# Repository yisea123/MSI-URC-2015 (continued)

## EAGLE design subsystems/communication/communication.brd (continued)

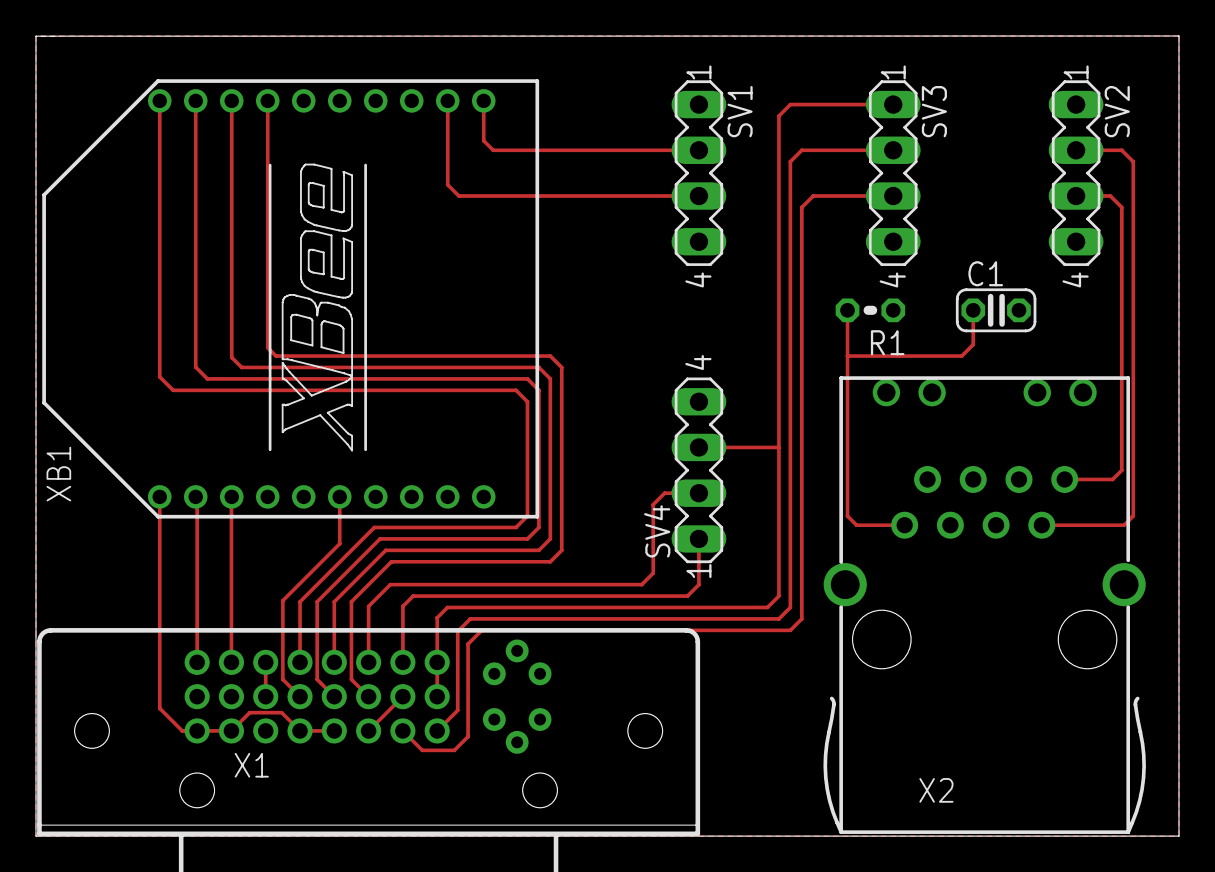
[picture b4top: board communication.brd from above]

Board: 2 copper layers, 63.5 x 44.5 mm, 9 parts (0 on the bottom side), 19 nets.

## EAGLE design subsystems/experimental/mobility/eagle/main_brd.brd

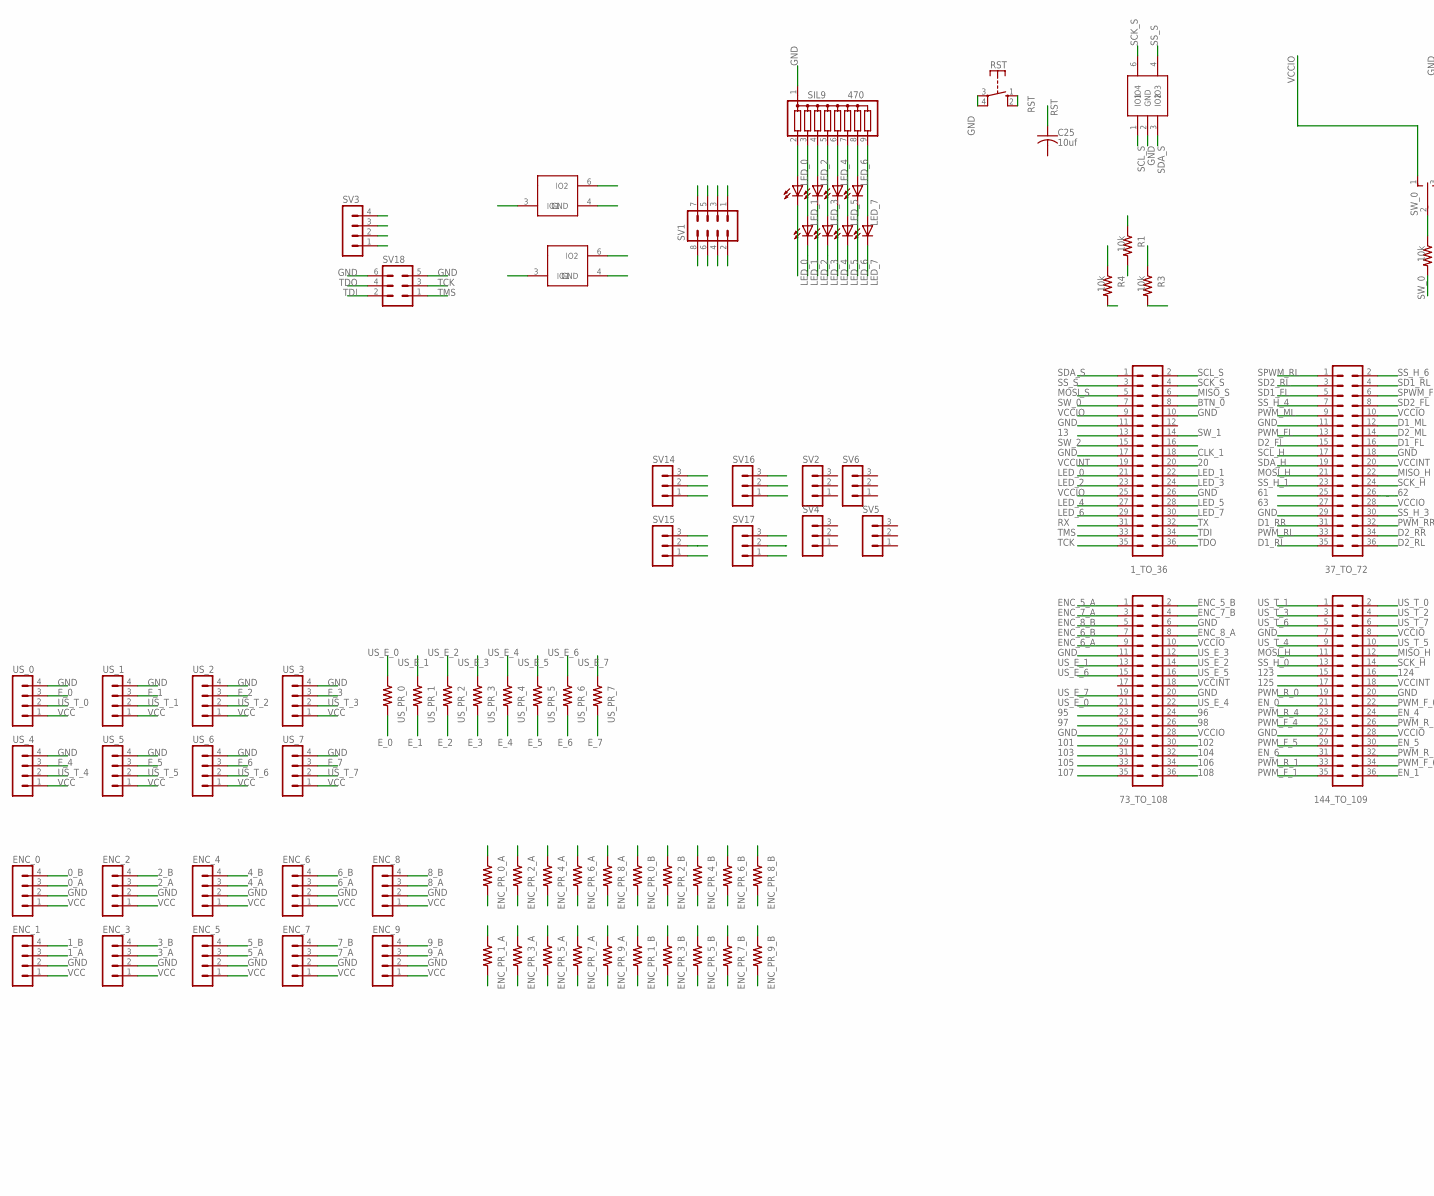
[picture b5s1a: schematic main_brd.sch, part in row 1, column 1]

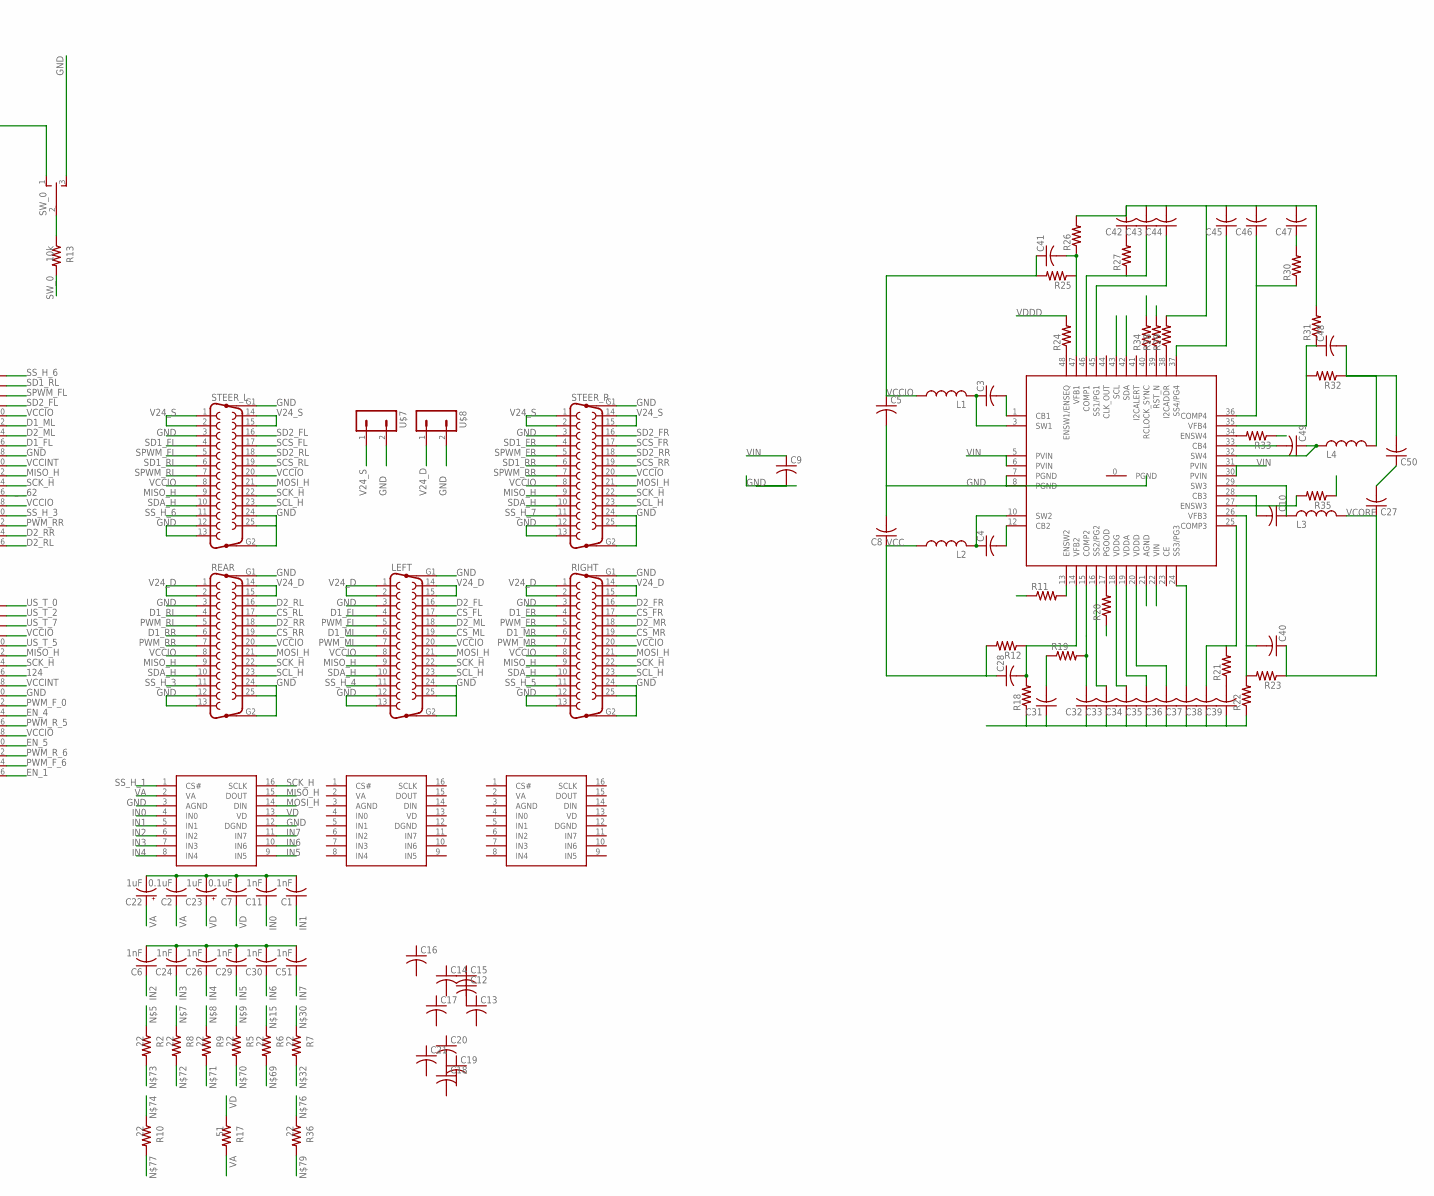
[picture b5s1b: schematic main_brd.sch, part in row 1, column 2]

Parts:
1_TO_36, 37_TO_72, 73_TO_108, 144_TO_109: MA18-2
C1, C6, C11, C24, C26, C29, C30, C51: 1nF; C1206
C2, C7: 0.1uF; C1206
C3, C4, C5, C8, C9, C10, C12, C13, C14, C15, C16, C17, C18, C19, C20, C21, C27, C28, C31, C32, C33, C34, C35, C36, C37, C38, C39, C40, C41, C42, C43, C44, C45, C46, C47, C48, C49, C50: C-USC1206; C1206
C22, C23: 1uF; E1,8-4
C25: 10uf; C1206
ENC_0, ENC_1, ENC_2, ENC_3, ENC_4, ENC_5, ENC_6, ENC_7, ENC_8, ENC_9: MA04-1
ENC_PR_0_A, ENC_PR_0_B, ENC_PR_1_A, ENC_PR_1_B, ENC_PR_2_A, ENC_PR_2_B, ENC_PR_3_A, ENC_PR_3_B, ENC_PR_4_A, ENC_PR_4_B, ENC_PR_5_A, ENC_PR_5_B, ENC_PR_6_A, ENC_PR_6_B, ENC_PR_7_A, ENC_PR_7_B, ENC_PR_8_A, ENC_PR_8_B, ENC_PR_9_A, ENC_PR_9_B: R-US_R1206; R1206
L1, L2, L3, L4: L-USL1206; C1206
LED_0, LED_1, LED_2, LED_3, LED_4, LED_5, LED_6, LED_7: LEDSMT1206; 1206
LEFT: F25HP
R1, R3, R4, R13: 10k; R1206
R2, R5, R6, R7, R8, R9, R10, R36: 22; R1206
R11, R12, R18, R19, R20, R21, R22, R23, R24, R25, R26, R27, R28, R29, R30, R31, R32, R33, R34, R35: R-US_R1206; R1206
R17: 51; R1206
REAR: F25HP
RIGHT: F25HP
RST: RACON12
SIL9: 470; SIL9
STEER_L: F25HP
STEER_R: F25HP
SV1: MA04-2
SV2, SV4, SV5, SV6, SV14, SV15, SV16, SV17: MA03-1
SV3: MA04-1
SV18: MA03-2
SW_0: TL39PO; TL3XPO
U$1: TPD4E1B06DCKR; DCK6
U$2: TPS65400RGZR; VQFN48
U$4, U$5: TPD2E2U06DRLR; DRL5
U$7, U$8: MB02-1; MB03-1
U$9, U$10, U$11: ADC128S052QCMT; R-PDSO-G16
US_0, US_1, US_2, US_3, US_4, US_5, US_6, US_7: MA04-1
US_PR_0, US_PR_1, US_PR_2, US_PR_3, US_PR_4, US_PR_5, US_PR_6, US_PR_7: R-US_R1206; R1206

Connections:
0_A: ENC_0.3, ENC_PR_0_A.2
0_B: ENC_0.4, ENC_PR_0_B.2
1_A: ENC_1.3, ENC_PR_1_A.2
1_B: ENC_1.4, ENC_PR_1_B.2
2_A: ENC_2.3, ENC_PR_2_A.2
2_B: ENC_2.4, ENC_PR_2_B.2
3_A: ENC_3.3, ENC_PR_3_A.2
3_B: ENC_3.4, ENC_PR_3_B.2
4_A: ENC_4.3, ENC_PR_4_A.2
4_B: ENC_4.4, ENC_PR_4_B.2
5_A: ENC_5.3, ENC_PR_5_A.2
5_B: ENC_5.4, ENC_PR_5_B.2
6_A: ENC_6.3, ENC_PR_6_A.2
6_B: ENC_6.4, ENC_PR_6_B.2
7_A: ENC_7.3, ENC_PR_7_A.2
7_B: ENC_7.4, ENC_PR_7_B.2
8_A: ENC_8.3, ENC_PR_8_A.2
8_B: ENC_8.4, ENC_PR_8_B.2
9_A: ENC_9.3, ENC_PR_9_A.2
9_B: ENC_9.4, ENC_PR_9_B.2
13: 1_TO_36.13
20: 1_TO_36.20
61: 37_TO_72.25
62: 37_TO_72.26
63: 37_TO_72.27
95: 73_TO_108.23
96: 73_TO_108.24
97: 73_TO_108.25
98: 73_TO_108.26
101: 73_TO_108.29
102: 73_TO_108.30
103: 73_TO_108.31
104: 73_TO_108.32
105: 73_TO_108.33
106: 73_TO_108.34
107: 73_TO_108.35
108: 73_TO_108.36
123: 144_TO_109.15
124: 144_TO_109.16
125: 144_TO_109.17
BTN: U$4.6 (IO2)
BTN_0: 1_TO_36.8
CLK_1: 1_TO_36.18
CS_FL: LEFT.17
CS_FR: RIGHT.17
CS_ML: LEFT.19
CS_MR: RIGHT.19
CS_RL: REAR.17
CS_RR: REAR.19
D1_FL: 37_TO_72.16, LEFT.4
D1_FR: RIGHT.4
D1_ML: 37_TO_72.12, LEFT.6
D1_MR: RIGHT.6
D1_RL: 37_TO_72.35, REAR.4
D1_RR: 37_TO_72.31, REAR.6
D2_FL: 37_TO_72.15, LEFT.16
D2_FR: RIGHT.16
D2_ML: 37_TO_72.14, LEFT.18
D2_MR: RIGHT.18
D2_RL: 37_TO_72.36, REAR.16
D2_RR: 37_TO_72.34, REAR.18
ENC_0_A: ENC_PR_0_A.1
ENC_0_B: ENC_PR_0_B.1
ENC_1_A: ENC_PR_1_A.1
ENC_1_B: ENC_PR_1_B.1
ENC_2_A: ENC_PR_2_A.1
ENC_2_B: ENC_PR_2_B.1
ENC_3_A: ENC_PR_3_A.1
ENC_3_B: ENC_PR_3_B.1
ENC_4_A: ENC_PR_4_A.1
ENC_4_B: ENC_PR_4_B.1
ENC_5_A: 73_TO_108.1, ENC_PR_5_A.1
ENC_5_B: 73_TO_108.2, ENC_PR_5_B.1
ENC_6_A: 73_TO_108.9, ENC_PR_6_A.1
ENC_6_B: 73_TO_108.7, ENC_PR_6_B.1
ENC_7_A: 73_TO_108.3, ENC_PR_7_A.1
ENC_7_B: 73_TO_108.4, ENC_PR_7_B.1
ENC_8_A: 73_TO_108.8, ENC_PR_8_A.1
ENC_8_B: 73_TO_108.5, ENC_PR_8_B.1
ENC_9_A: ENC_PR_9_A.1
ENC_9_B: ENC_PR_9_B.1
ENSW3: R35.2, U$2.27 (ENSW3)
ENSW4: R33.2, U$2.34 (ENSW4)
EN_0: 144_TO_109.21
EN_1: 144_TO_109.36
EN_4: 144_TO_109.24
EN_5: 144_TO_109.30
EN_6: 144_TO_109.31
E_0: US_0.3, US_PR_0.2
E_1: US_1.3, US_PR_1.2
E_2: US_2.3, US_PR_2.2
E_3: US_3.3, US_PR_3.2
E_4: US_4.3, US_PR_4.2
E_5: US_5.3, US_PR_5.2
E_6: US_6.3, US_PR_6.2
E_7: US_7.3, US_PR_7.2
GND: 1_TO_36.10, 1_TO_36.11, 1_TO_36.17, 1_TO_36.26, 37_TO_72.11, 37_TO_72.18, 37_TO_72.29, 73_TO_108.6, 73_TO_108.11, 73_TO_108.20, 73_TO_108.27, 144_TO_109.7, 144_TO_109.20, 144_TO_109.27, C1.2, C2.2, C5.2, C7.2, C8.2, C9.2, C11.2, C22.-, C23.-, C27.2, C31.1, C32.1, C33.1, C34.1, C35.1, C36.1, C37.1, C38.1, C39.1, C42.2, C43.2, C44.2, C45.2, C46.2, C47.2, ENC_0.2, ENC_1.2, ENC_2.2, ENC_3.2, ENC_4.2, ENC_5.2, ENC_6.2, ENC_7.2, ENC_8.2, ENC_9.2, LEFT.3, LEFT.12, LEFT.13, LEFT.24, LEFT.25, LEFT.G1, LEFT.G2, R18.1, R22.1, R26.2, R29.2, R31.2, R34.2, REAR.3, REAR.12, REAR.13, REAR.24, REAR.25, REAR.G1, REAR.G2, RIGHT.3, RIGHT.12, RIGHT.13, RIGHT.24, RIGHT.25, RIGHT.G1, RIGHT.G2, RST.3, RST.4, SIL9.1, STEER_L.3, STEER_L.12, STEER_L.13, STEER_L.24, STEER_L.25, STEER_L.G1, STEER_L.G2, STEER_R.3, STEER_R.12, STEER_R.13, STEER_R.24, STEER_R.25, STEER_R.G1, STEER_R.G2, SV1.7, SV1.8, SV3.2, SV14.3, SV15.3, SV16.3, SV17.3, SV18.5, SV18.6, SW_0.3 (S), U$1.2 (GND), U$2.7 (PGND), U$2.8 (PGND), U$2.21 (AGND), U$4.4 (GND), U$5.4 (GND), U$7.2, U$8.2, U$9.3 (AGND), U$9.12 (DGND), US_0.4, US_1.4, US_2.4, US_3.4, US_4.4, US_5.4, US_6.4, US_7.4
IN0: C11.1, U$9.4 (IN0)
IN1: C1.1, U$9.5 (IN1)
IN2: C6.1, U$9.6 (IN2)
IN3: C24.1, U$9.7 (IN3)
IN4: C26.1, U$9.8 (IN4)
IN5: C29.1, U$9.9 (IN5)
IN6: C30.1, U$9.10 (IN6)
IN7: C51.1, U$9.11 (IN7)
LED_0: 1_TO_36.21, LED_0.C
LED_1: 1_TO_36.22, LED_1.C
LED_2: 1_TO_36.23, LED_2.C
LED_3: 1_TO_36.24, LED_3.C
LED_4: 1_TO_36.27, LED_4.C
LED_5: 1_TO_36.28, LED_5.C
LED_6: 1_TO_36.29, LED_6.C
LED_7: 1_TO_36.30, LED_7.C
MISO_H: 37_TO_72.22, 144_TO_109.12, LEFT.9, REAR.9, RIGHT.9, STEER_L.9, STEER_R.9, U$9.15 (DOUT)
MISO_S: 1_TO_36.6, SV1.5, U$5.3 (IO1)
MOSI_H: 37_TO_72.21, 144_TO_109.11, LEFT.21, REAR.21, RIGHT.21, STEER_L.21, STEER_R.21, U$9.14 (DIN)
MOSI_S: 1_TO_36.5, SV1.6, U$5.6 (IO2)
unnamed: C4.1, L2.2, U$2.10 (SW2)
unnamed: C18.1, C20.2
unnamed: C3.2, U$2.1 (CB1)
unnamed: C3.1, L1.2, U$2.3 (SW1)
unnamed: C4.2, U$2.12 (CB2)
unnamed: C10.1, L3.2, U$2.29 (SW3)
unnamed: C10.2, U$2.28 (CB3)
unnamed: R11.2, U$2.13 (ENSW2)
unnamed: C28.2, R12.1, R18.2, U$2.14 (VFB2)
unnamed: C32.2, R19.2, U$2.15 (COMP2)
unnamed: LED_0.A, SIL9.2
unnamed: LED_4.A, SIL9.6
unnamed: LED_6.A, SIL9.8
unnamed: LED_1.A, SIL9.3
unnamed: LED_3.A, SIL9.5
unnamed: LED_5.A, SIL9.7
unnamed: LED_7.A, SIL9.9
unnamed: C31.2, R19.1
unnamed: R13.1, SW_0.2
unnamed: R20.2, U$2.17 (PGOOD)
unnamed: C6.2, C24.2, C26.2, C29.2, C30.2, C51.2
unnamed: C34.2, U$2.18 (VDDG)
unnamed: C35.2, U$2.19 (VDDA)
unnamed: C39.2, R21.1
unnamed: C40.2, R22.2, R23.2, U$2.26 (VFB3)
unnamed: C38.2, R21.2, U$2.25 (COMP3)
unnamed: R24.1, U$2.48 (ENSW1/ENSEQ)
unnamed: C37.2, U$2.24 (SS3/PG3)
unnamed: C33.2, U$2.16 (SS2/PG2)
unnamed: C42.1, R27.2
unnamed: R29.1, U$2.38 (I2CADDR)
unnamed: C48.1, R31.1, R32.2, U$2.35 (VFB4)
unnamed: C49.1, L4.2, U$2.32 (SW4)
unnamed: C41.2, R25.1, R26.1, U$2.47 (VFB1)
unnamed: C45.1, U$2.37 (SS4/PG4)
unnamed: C46.1, R30.1, U$2.36 (COMP4)
unnamed: C47.1, R30.2
unnamed: C43.1, R27.1, U$2.46 (COMP1)
unnamed: C44.1, U$2.45 (SS1/PG1)
unnamed: C49.2, U$2.33 (CB4)
unnamed: R34.1, U$2.40 (RCLOCK_SYNC)
POT_0: SV14.2
POT_1: SV15.2
POT_2: SV16.2
POT_3: SV17.2
PWM_FL: 37_TO_72.13, LEFT.5
PWM_FR: RIGHT.5
PWM_F_0: 144_TO_109.22
PWM_F_1: 144_TO_109.35
PWM_F_4: 144_TO_109.25
PWM_F_5: 144_TO_109.29
PWM_F_6: 144_TO_109.34
PWM_ML: 37_TO_72.9, LEFT.7
PWM_MR: RIGHT.7
PWM_RL: 37_TO_72.33, REAR.5
PWM_RR: 37_TO_72.32, REAR.7
PWM_R_0: 144_TO_109.19
PWM_R_1: 144_TO_109.33
PWM_R_4: 144_TO_109.23
PWM_R_5: 144_TO_109.26
PWM_R_6: 144_TO_109.32
RST: C25.1, R1.1, RST.1 (S), RST.2 (S), U$4.3 (IO1)
RST_N: R28.1, U$2.39 (RST_N)
RX: 1_TO_36.31, SV3.3
SCK_H: 37_TO_72.24, 144_TO_109.14, LEFT.22, REAR.22, RIGHT.22, STEER_L.22, STEER_R.22, U$9.16 (SCLK)
SCK_S: 1_TO_36.4, SV1.3, U$1.6 (IO4)
SCL_H: 37_TO_72.17, LEFT.23, REAR.23, RIGHT.23, STEER_L.23, STEER_R.23
SCL_S: 1_TO_36.2, R4.1, SV1.1, U$1.1 (IO1), U$2.43 (SCL)
SCS_FL: STEER_L.17
SCS_FR: STEER_R.17
SCS_RL: STEER_L.19
SCS_RR: STEER_R.19
SD1_FL: 37_TO_72.5, STEER_L.4
SD1_FR: STEER_R.4
SD1_RL: 37_TO_72.4, STEER_L.6
SD1_RR: STEER_R.6
SD2_FL: 37_TO_72.8, STEER_L.16
SD2_FR: STEER_R.16
SD2_RL: 37_TO_72.3, STEER_L.18
SD2_RR: STEER_R.18
SDA_H: 37_TO_72.19, LEFT.10, REAR.10, RIGHT.10, STEER_L.10, STEER_R.10
SDA_S: 1_TO_36.1, R3.1, SV1.2, U$1.3 (IO2), U$2.42 (SDA)
SIL10: LED_2.A, SIL9.4
SPWM_FL: 37_TO_72.6, STEER_L.5
SPWM_FR: STEER_R.5
SPWM_RL: 37_TO_72.1, STEER_L.7
SPWM_RR: STEER_R.7
SS_H_0: 144_TO_109.13
SS_H_1: 37_TO_72.23, U$9.1 (CS#)
SS_H_3: 37_TO_72.30, REAR.11
SS_H_4: 37_TO_72.7, LEFT.11
SS_H_5: RIGHT.11
SS_H_6: 37_TO_72.2, STEER_L.11
SS_H_7: STEER_R.11
SS_S: 1_TO_36.3, SV1.4, U$1.4 (IO3)
SW_0: 1_TO_36.7, R13.2
SW_1: 1_TO_36.14
SW_2: 1_TO_36.15
SW_3: 1_TO_36.16
TCK: 1_TO_36.35, SV18.3
TDI: 1_TO_36.34, SV18.2
TDO: 1_TO_36.36, SV18.4
TMS: 1_TO_36.33, SV18.1
TX: 1_TO_36.32, SV3.1
US_E_0: 73_TO_108.21, US_PR_0.1
US_E_1: 73_TO_108.13, US_PR_1.1
US_E_2: 73_TO_108.14, US_PR_2.1
US_E_3: 73_TO_108.12, US_PR_3.1
US_E_4: 73_TO_108.22, US_PR_4.1
US_E_5: 73_TO_108.16, US_PR_5.1
US_E_6: 73_TO_108.15, US_PR_6.1
US_E_7: 73_TO_108.19, US_PR_7.1
US_T_0: 144_TO_109.2, US_0.2
US_T_1: 144_TO_109.1, US_1.2
US_T_2: 144_TO_109.4, US_2.2
US_T_3: 144_TO_109.3, US_3.2
US_T_4: 144_TO_109.9, US_4.2
US_T_5: 144_TO_109.10, US_5.2
US_T_6: 144_TO_109.5, US_6.2
US_T_7: 144_TO_109.6, US_7.2
V24_D: LEFT.1, LEFT.2, LEFT.14, LEFT.15, REAR.1, REAR.2, REAR.14, REAR.15, RIGHT.1, RIGHT.2, RIGHT.14, RIGHT.15, U$8.1
V24_S: STEER_L.1, STEER_L.2, STEER_L.14, STEER_L.15, STEER_R.1, STEER_R.2, STEER_R.14, STEER_R.15, U$7.1
VA: C2.1, C22.+, R17.2, U$9.2 (VA)
VCC: C8.1, C28.1, ENC_0.1, ENC_1.1, ENC_2.1, ENC_3.1, ENC_4.1, ENC_5.1, ENC_6.1, ENC_7.1, ENC_8.1, ENC_9.1, L2.1, R12.2, SV14.1, SV15.1, SV16.1, SV17.1, US_0.1, US_1.1, US_2.1, US_3.1, US_4.1, US_5.1, US_6.1, US_7.1
VCCINT: 1_TO_36.19, 37_TO_72.20, 73_TO_108.18, 144_TO_109.18, C48.2, C50.2, L4.1, R32.1
VCCIO: 1_TO_36.9, 1_TO_36.25, 37_TO_72.10, 37_TO_72.28, 73_TO_108.10, 73_TO_108.28, 144_TO_109.8, 144_TO_109.28, C5.1, C41.1, L1.1, LEFT.8, LEFT.20, R1.2, R3.2, R4.2, R25.2, REAR.8, REAR.20, RIGHT.8, RIGHT.20, STEER_L.8, STEER_L.20, STEER_R.8, STEER_R.20, SV3.4, SW_0.1 (O)
VCORE: C27.1, C40.1, L3.1, R23.1
VD: C7.1, C23.+, R17.1, U$9.13 (VD)
VDDD: C36.2, R11.1, R20.1, R24.2, R28.2, R33.1, R35.1, U$2.20 (VDDD)
VIN: C9.1, U$2.5 (PVIN), U$2.6 (PVIN), U$2.22 (VIN), U$2.30 (PVIN), U$2.31 (PVIN)

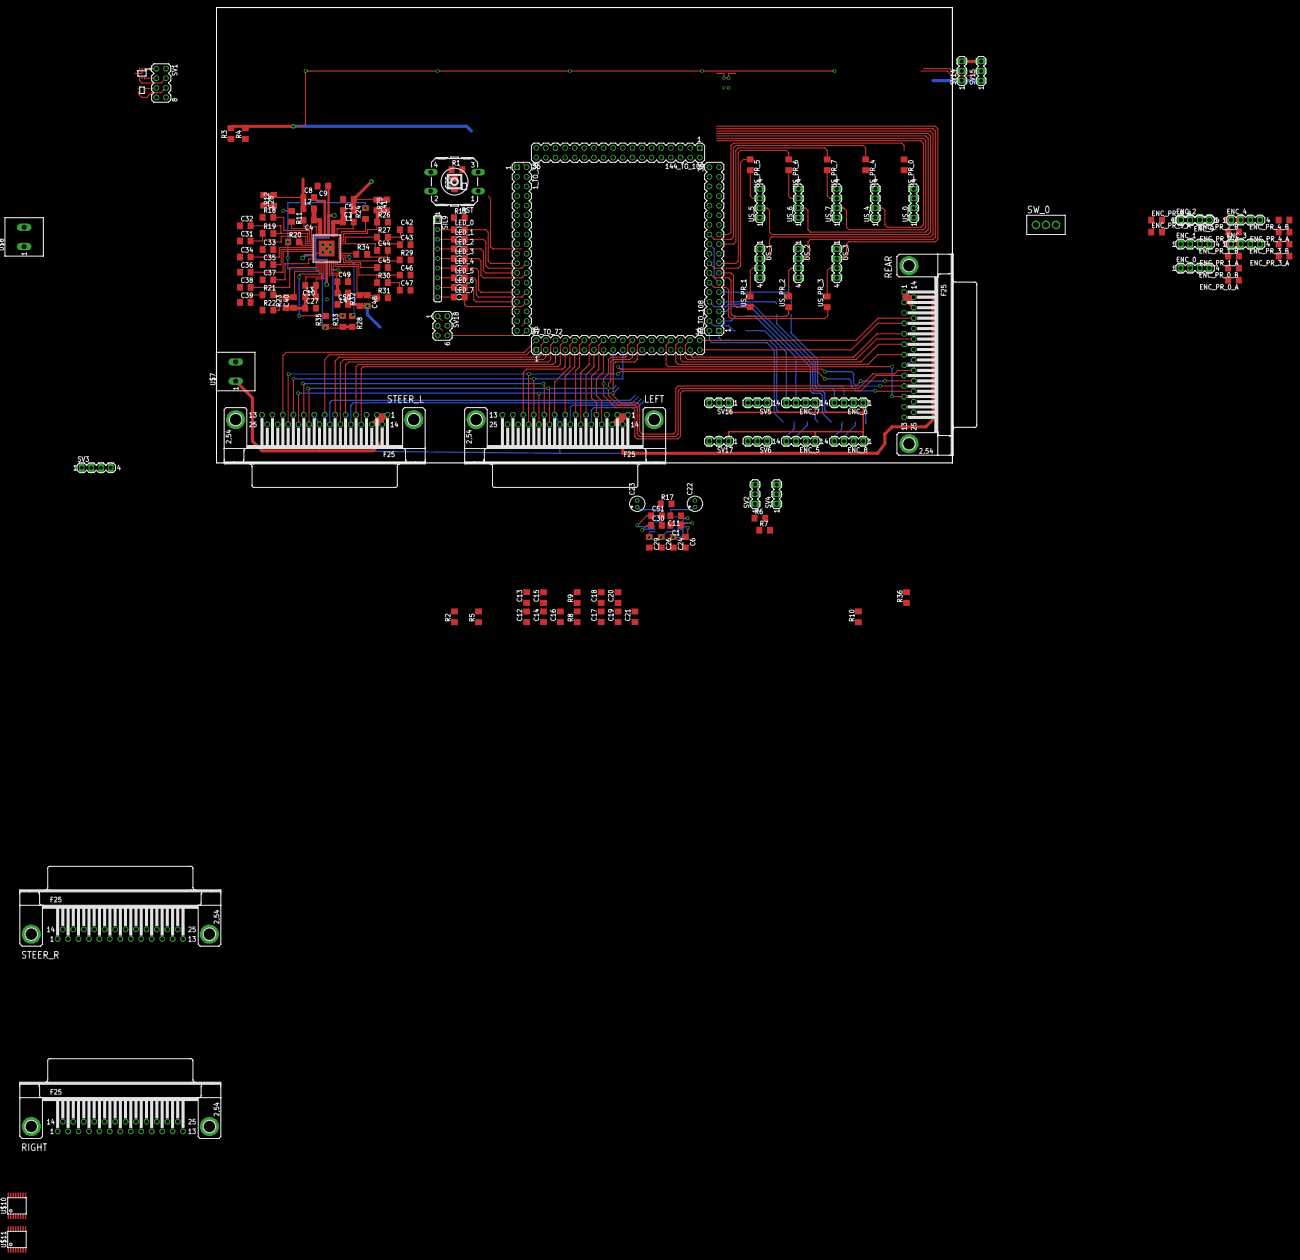
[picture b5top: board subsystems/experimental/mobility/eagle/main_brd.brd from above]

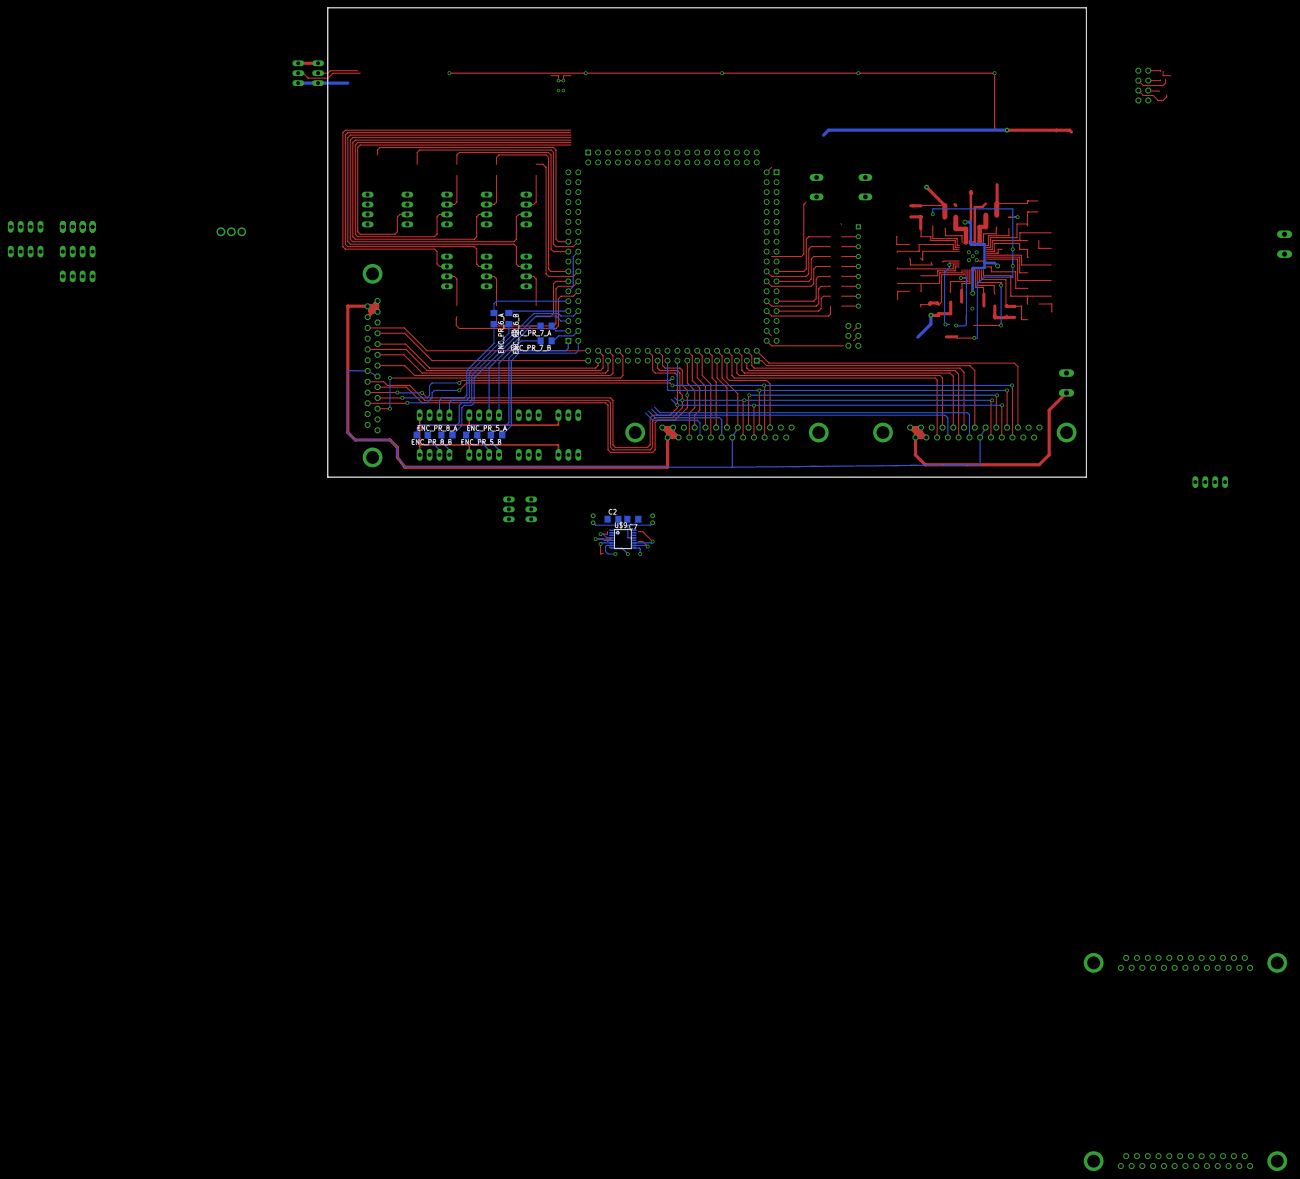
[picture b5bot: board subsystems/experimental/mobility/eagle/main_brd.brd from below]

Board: 2 copper layers, 194.4 x 120.3 mm, 174 parts (11 on the bottom side), 165 nets.

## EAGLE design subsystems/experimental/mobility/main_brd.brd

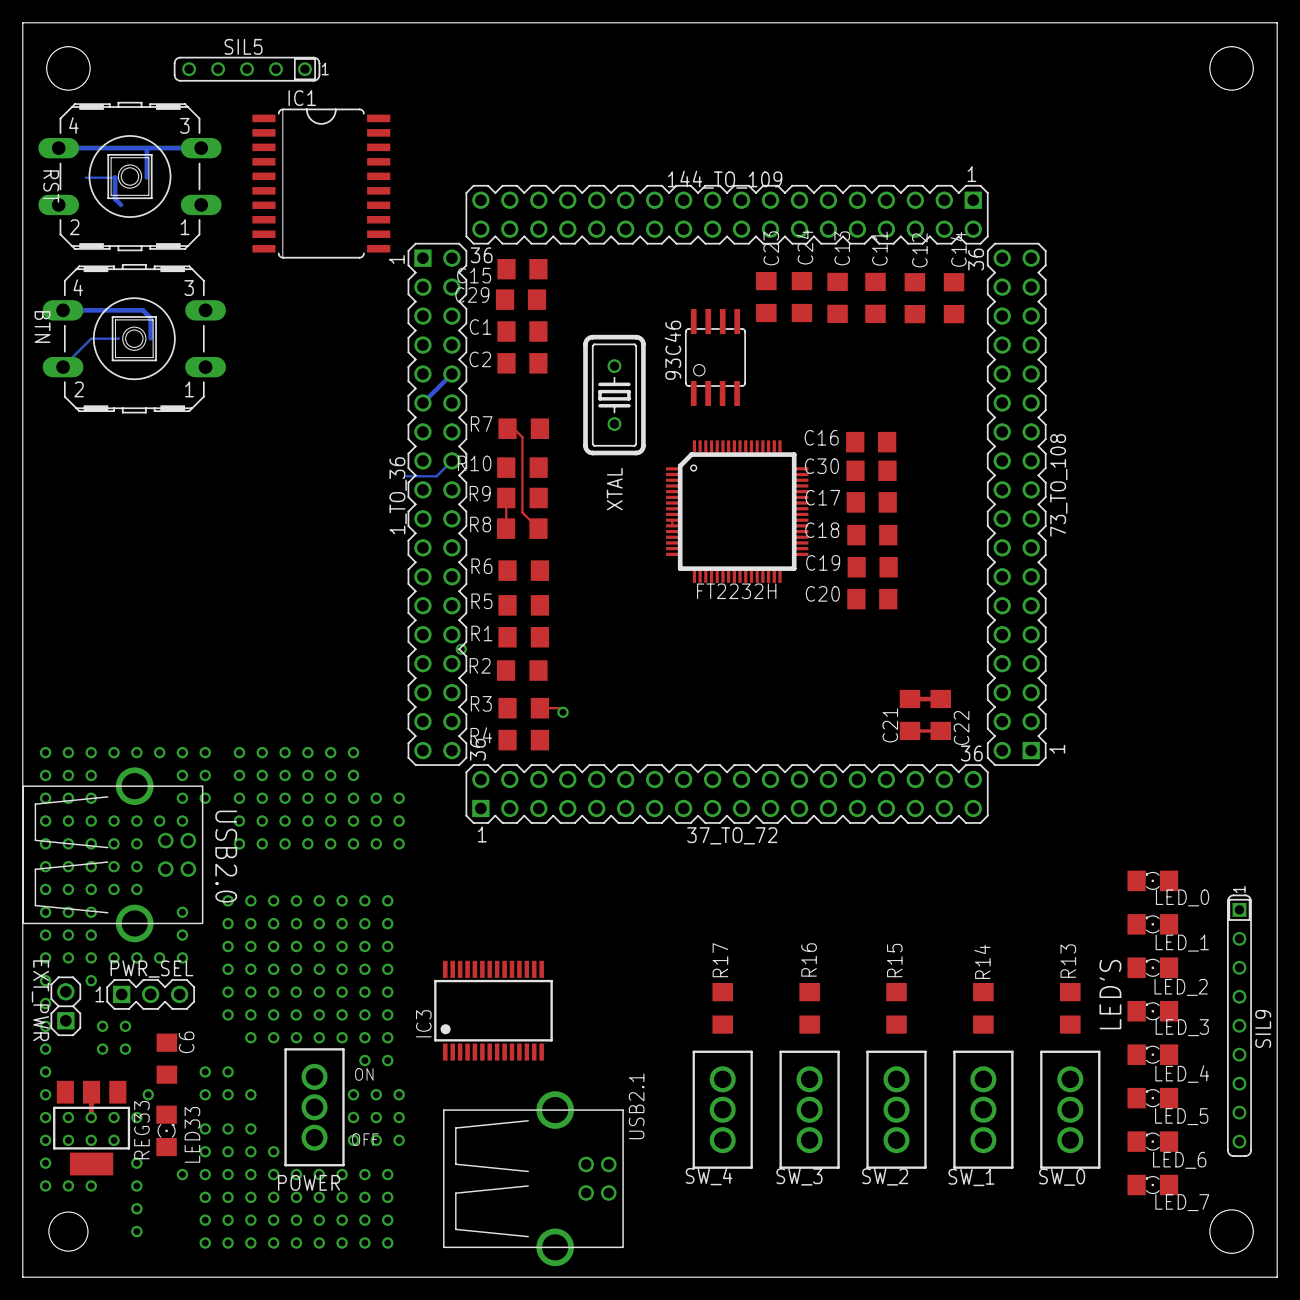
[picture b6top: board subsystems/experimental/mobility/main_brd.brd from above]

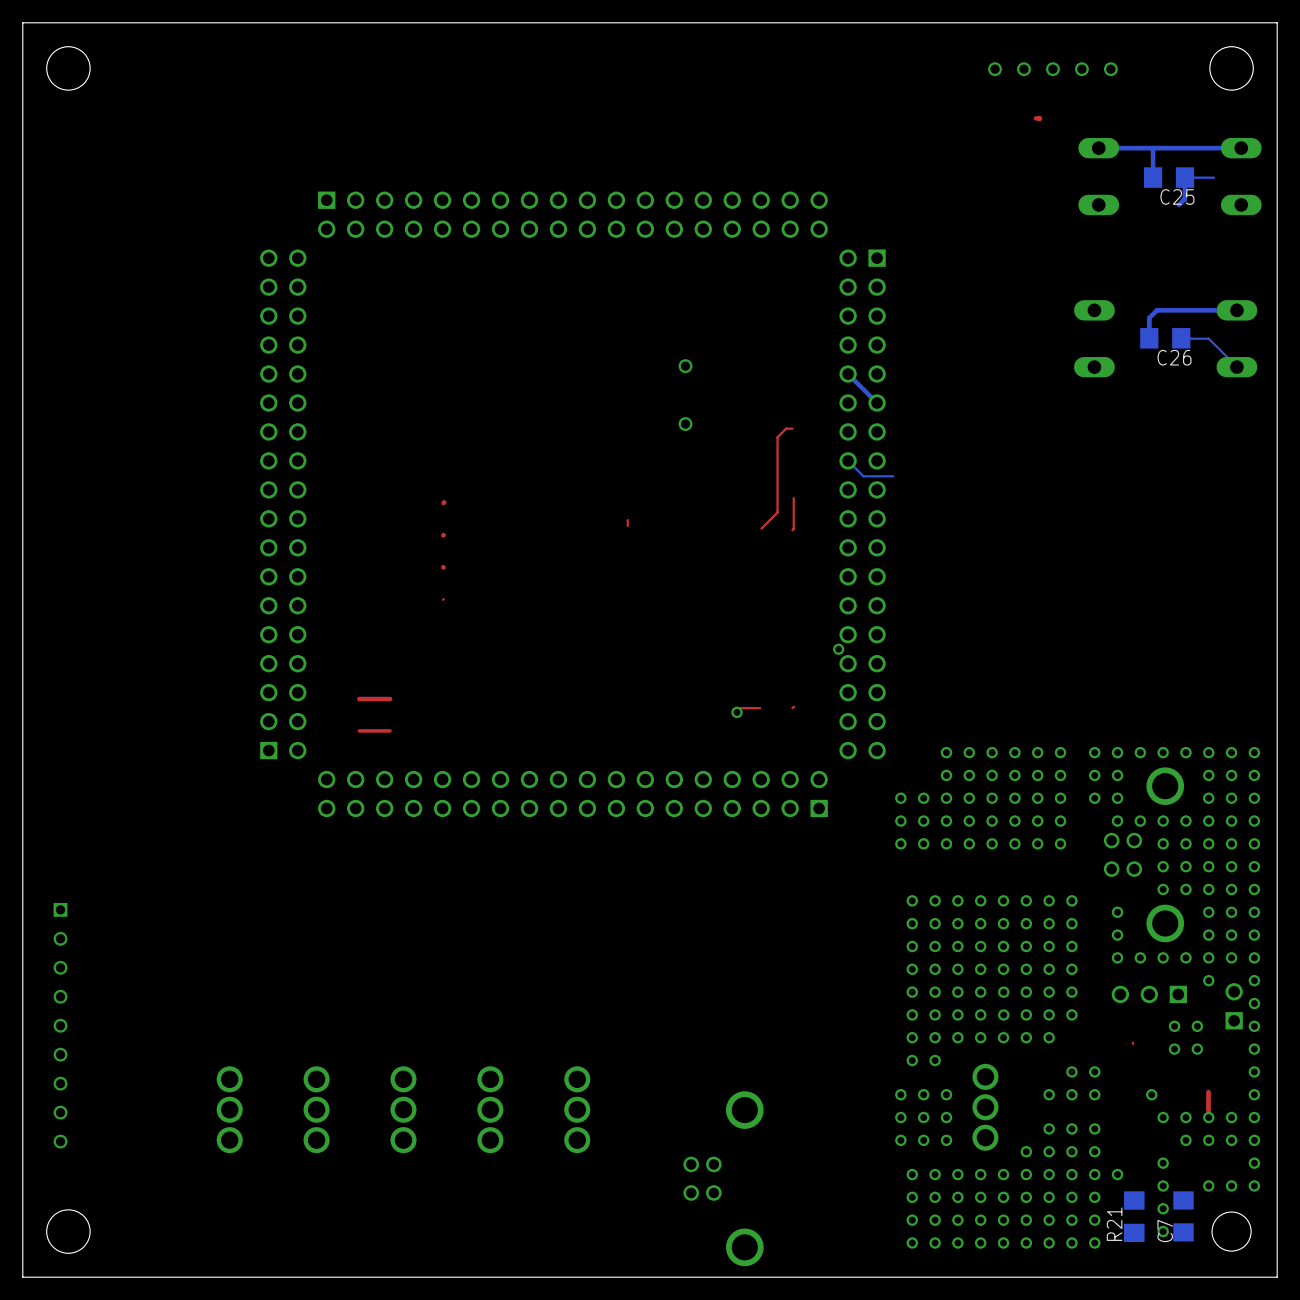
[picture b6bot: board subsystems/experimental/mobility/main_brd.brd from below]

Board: 2 copper layers, 110.0 x 110.0 mm, 71 parts (4 on the bottom side), 51 nets.

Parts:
1_TO_36, 37_TO_72, 73_TO_108, 144_TO_109: MA18-2
93C46: SOIC8
BTN: RACON12
C1, C2: 27pf; C1206
C6, C7, C17, C18, C19, C20, C21, C22, C23, C24: 100nf; C1206
C11, C12, C29, C30: 3.3uf; C1206
C13, C14, C15, C16: 4.7uf; C1206
C25, C26: 10uf; C1206
EXT_PWR: 1X02
FT2232H: FT2232H; LQFP_NEW
IC1: 74LS245DW; SO20W
IC3: FT232RL; SSOP28
LED33: 1206
LED_0, LED_1, LED_2, LED_3, LED_4, LED_5, LED_6, LED_7: 1206
POWER: TL3XPO
PWR_SEL: MA03-1
R1, R6: 1k; R1206
R2, R3, R4, R8, R9, R10, R13, R14, R15, R16, R17: 10k; R1206
R5: 12k; R1206
R7: 2.2k; R1206
R21: 470; R1206
REG33: SOT223
RST: RACON12
SIL5: 10k; SIL5
SIL9: 470; SIL9
SW_0, SW_1, SW_2, SW_3, SW_4: TL3XPO
USB2.0, USB2.1: USB-B-H
XTAL: 16MHz; HC18U-V

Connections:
57: 37_TO_72.21, LED_1.C
58: 37_TO_72.22, LED_0.C
BTN: BTN.1, BTN.2, C26.1, IC1.3, SIL5.5
BTN_0: 1_TO_36.1, IC1.18
BTN_1: 1_TO_36.2, IC1.17
D+: FT2232H.8, USB2.0.D+
D-: FT2232H.7, USB2.0.D-
EECLK: 93C46.2, FT2232H.62, R10.1
EECS: 93C46.1, FT2232H.63, R9.1
EEDATA: 93C46.3, FT2232H.61, R7.2
GND: 1_TO_36.10, 1_TO_36.11, 1_TO_36.17, 1_TO_36.26, 37_TO_72.11, 37_TO_72.18, 37_TO_72.29, 73_TO_108.6, 73_TO_108.11, 73_TO_108.20, 73_TO_108.27, 93C46.5, 93C46.7, 144_TO_109.7, 144_TO_109.20, 144_TO_109.27, BTN.3, BTN.4, C1.2, C2.2, C6.2, C7.2, C11.2, C12.2, C13.2, C14.2, C15.2, C16.2, C17.2, C18.2, C19.2, C20.2, C21.2, C22.2, C23.2, C24.2, C25.2, C26.2, C29.2, C30.2, EXT_PWR.1, FT2232H.1, FT2232H.5, FT2232H.10, FT2232H.11, FT2232H.13, FT2232H.15, FT2232H.25, FT2232H.35, FT2232H.47, FT2232H.51, IC1.10, IC1.19, IC3.7, IC3.18, IC3.21, IC3.25, IC3.26, LED33.C, POWER.1, R1.2, R5.1, REG33.1, RST.3, RST.4, SIL9.1, SW_0.3, SW_1.3, SW_2.3, SW_3.3, SW_4.3, USB2.0.GND, USB2.1.GND
unnamed: C1.1, FT2232H.2, XTAL.2
unnamed: IC3.15, USB2.1.D+
unnamed: LED33.A, R21.2
unnamed: IC3.16, USB2.1.D-
unnamed: FT2232H.6, R5.2
unnamed: FT2232H.14, R6.2
unnamed: IC3.4, IC3.17
unnamed: 93C46.4, R7.1, R8.1
unnamed: LED_0.A, SIL9.2
unnamed: LED_4.A, SIL9.6
unnamed: LED_6.A, SIL9.8
unnamed: LED_1.A, SIL9.3
unnamed: LED_3.A, SIL9.5
unnamed: LED_5.A, SIL9.7
unnamed: LED_7.A, SIL9.9
unnamed: R13.1, SW_0.2
unnamed: R14.1, SW_1.2
unnamed: R15.1, SW_2.2
unnamed: R16.1, SW_3.2
unnamed: R17.1, SW_4.2
unnamed: EXT_PWR.2, PWR_SEL.1
OSCO: C2.1, FT2232H.3, XTAL.1
RST: C25.1, IC1.2, RST.1, RST.2, SIL5.4
SCL_S: 1_TO_36.7, SIL5.3
SDA_S: 1_TO_36.8, SIL5.2
SIL10: LED_2.A, SIL9.4
SW_0: 1_TO_36.12, R13.2
SW_1: 1_TO_36.13, R14.2
SW_2: 1_TO_36.14, R15.2
SW_3: 1_TO_36.15, R16.2
SW_4: 1_TO_36.16, R17.2
TCK: 1_TO_36.35, FT2232H.16, R1.1
TDI: 1_TO_36.34, FT2232H.17, R2.1
TDO: 1_TO_36.36, FT2232H.18, R3.1
TMS: 1_TO_36.33, FT2232H.19, R4.1
VBUS: PWR_SEL.3, USB2.0.VBUS, USB2.1.VBUS
VCC: C6.1, POWER.2, REG33.3
VCCINT: 1_TO_36.19, 37_TO_72.20, 73_TO_108.18, 144_TO_109.18, C11.1, C12.1, C15.1, C16.1, C21.1, C22.1, C23.1, C24.1, FT2232H.12, FT2232H.37, FT2232H.49, FT2232H.64
VCCIO: 1_TO_36.9, 1_TO_36.25, 37_TO_72.10, 37_TO_72.28, 73_TO_108.10, 73_TO_108.28, 93C46.6, 93C46.8, 144_TO_109.8, 144_TO_109.28, C7.1, C13.1, C14.1, C17.1, C18.1, C19.1, C20.1, C29.1, C30.1, FT2232H.4, FT2232H.9, FT2232H.20, FT2232H.31, FT2232H.42, FT2232H.50, FT2232H.56, IC1.1, IC1.20, R2.2, R3.2, R4.2, R6.1, R8.2, R9.2, R10.2, R21.1, REG33.4, SIL5.1, SW_0.1, SW_1.1, SW_2.1, SW_3.1, SW_4.1
XXX: POWER.3, PWR_SEL.2

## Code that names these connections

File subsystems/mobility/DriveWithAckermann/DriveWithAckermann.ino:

#define H1 1.0
#define H3 1.0
#define r1 1.0
#define r3 1.0
#define W1 1.0
#define W2 1.0
#define W3 1.0

#define FRWD 1
#define BKWD 0
#define ENC_RES 0.01  // in 10 um/count

struct state_t {
  float wheelSpeed[6];
  float steerAngle[4];
  boolean wheelDir[6];
};

struct motor_t {
  uint8_t ena;
  uint8_t dir;
  uint8_t pwm;
  boolean err;
};

struct encoder_t {
  uint8_t pin;
  int16_t position;
};

struct pot_t {
  uint8_t pin;
  uint8_t zero;
  uint8_t max;
  uint8_t min;
};

state_t currState = {{0,0,0,0,0,0}, {0,0,0,0}, {FRWD,FRWD,FRWD,FRWD,FRWD,FRWD}};
state_t destState = {{0,0,0,0,0,0}, {0,0,0,0}, {FRWD,FRWD,FRWD,FRWD,FRWD,FRWD}};
state_t nextState = {{0,0,0,0,0,0}, {0,0,0,0}, {FRWD,FRWD,FRWD,FRWD,FRWD,FRWD}};

//23 1DB2; 27 1DB1; A5 AB1; 3 PB1; 25 1DT2; 29 1DT1; NC AT1; 2 PT1
//47 3DB2; 45 3DB1; A9 AB3; 11 PB3; 46 3DT2; 44 3DT1; A8 AT3; 10 PT3

//43 4DB2; 41 4DB1; A7 AB4; 13 PB4; 42 4DT2; 40 4DT1; A6 AT4; 12 PT4
//39 5DB2; 37 5DB1; A0 AB5; 7  PB5; 38 5DT2; 36 4DT1; A1 AT5; 6  PT5
//35 6DB2; 34 6DB1; NC AB6; 5  PB6; 33 6DT2; 31 6DT1; NC AT6; 4  PT6

motor_t   driveMotor[6] = {{34, 35,  5, 0}, {31, 33,  4, 0}, {36, 38,  6, 0}, {41, 43, 13, 0}, {42, 40, 12, 0}, {37, 39,  7, 0}};
encoder_t encoder[6]    = {{22, 0},         {24, 0},         {26, 0},         {28, 0},         {30, 0},         {32, 0}     };

motor_t   steerMotor[6] = {{27, 23,  3, 0},      {29, 25,  2, 0},     {45, 47, 11, 0},     {44, 46, 10, 0}    };
pot_t     pot[4]        = {{ 9, 173,  308,  38}, { 4, 660, 525, 795}, {10, 458, 593, 323}, { 3, 555, 690, 420}};

unsigned long encUpdateTime = 0;

void onEncoder1Change() {
  (currState.wheelDir[1] == FRWD) ? encoder[1].position++ : encoder[1].position--;
};
void onEncoder4Change() {
  (currState.wheelDir[4] == FRWD) ? encoder[4].position++ : encoder[4].position--;
};

void wheelSpeedUpdate() {
  uint8_t time = millis() - encUpdateTime;
  float scale = ENC_RES / time;
  for( int i = 0; i < 6; i++) {
    currState.wheelSpeed[i] = encoder[i].position * scale;
    encoder[i].position = 0;
  }
  encUpdateTime = millis();
}

void speedFeedbackInit() {
  for( int i = 0; i < 6; i++) {
    pinMode(encoder[i].pin, INPUT);
  }
  
  attachInterrupt(encoder[0].pin, onEncoder1Change, RISING);
  attachInterrupt(encoder[1].pin, onEncoder1Change, RISING);
  attachInterrupt(encoder[2].pin, onEncoder1Change, RISING);
  attachInterrupt(encoder[3].pin, onEncoder1Change, RISING);
  attachInterrupt(encoder[4].pin, onEncoder1Change, RISING);
  attachInterrupt(encoder[5].pin, onEncoder1Change, RISING);

  encUpdateTime = millis();
}

void steerAnglesUpdate() {
  float ch;
  for( int i = 0; i < 4; i++ ) {
    ch = (unsigned int)(unsigned char)analogRead(pot[i].pin);
    ch = ch - pot[i].zero;
    //map
    currState.steerAngle[i] = ch;
    if (abs(ch) > 45) steerMotor[i].err = 1;
    Serial.print(ch);
    Serial.print("\t");
  }
  Serial.print("\n");
}

void potFeedbackInit() {
  for( int i = 0; i < 4; i++ ) {
    pinMode(pot[i].pin, INPUT);
  }
}

void destCompute(int16_t speed, int8_t encR, int8_t sigR) {
  float R, w;
  if(encR != 0) {
    R = sigR * 1023.0 / ( pow(2.0, encR / 25.0) - 1.0 );
    destState.steerAngle[0] = atan( H1 / ( R - W1/2 ) ) * 180 / PI;
    destState.steerAngle[1] = atan( H3 / ( R - W3/2 ) ) * 180 / PI;
    destState.steerAngle[2] = atan( H3 / ( R + W3/2 ) ) * 180 / PI;
    destState.steerAngle[3] = atan( H1 / ( R + W1/2 ) ) * 180 / PI;
 
    w = speed / R;
    destState.wheelSpeed[0] = w * (sqrt( pow(H1, 2) + pow(R - W1/2, 2) ) - r1);
    destState.wheelSpeed[1] = w * (R - W2/2);
    destState.wheelSpeed[2] = w * (sqrt( pow(H3, 2) + pow(R - W3/2, 2) ) - r3);
    destState.wheelSpeed[3] = w * (sqrt( pow(H3, 2) + pow(R + W3/2, 2) ) - r3);
    destState.wheelSpeed[4] = w * (R + W2/2);
    destState.wheelSpeed[5] = w * (sqrt( pow(H1, 2) + pow(R + W1/2, 2) ) - r1);
  }
  else {
    destState.steerAngle[0] = destState.steerAngle[1] = destState.steerAngle[2] = destState.steerAngle[3] = 0;
    destState.wheelSpeed[0] = destState.wheelSpeed[1] = destState.wheelSpeed[2] = destState.wheelSpeed[3] = destState.wheelSpeed[4] = destState.wheelSpeed[5] = speed;
  }
}

void motorsInit() {
  
}

void nextCompute() {
//decide  
}

void setup() {
  Serial.begin(9600);
  potFeedbackInit();
  speedFeedbackInit();
  //stateFeedbackInit();
  motorsInit();
}

void loop() {
  steerAnglesUpdate();
  wheelSpeedUpdate();
  //stateAngleUpdate();
  destCompute(200, 100, 1);
  nextCompute();
}

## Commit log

2014-09-08 Mary had a little lamb
2014-09-08 conflictcorrection
2014-09-08 guiOptionAdded
2014-09-08 something
2014-09-10 Updated gazebo.bash
2014-09-10 Deleted CAD.stl
2014-09-12 Updated Rover
2014-09-12 Added Arena
2014-09-17 k equal ok
2014-09-17 Include dir fix
2014-09-17 Reorganisation
2014-09-18 Navigation processing node template added
2014-09-19 Navigation skeleton final
2014-09-19 Updated arena.world
2014-09-19 navigation launchfile and initial parameters
2014-09-19 MapGen and odometry simulators created
2014-09-19 Added nav simulation files
2014-09-19 Aloo is not a `const`
2014-09-20 steering ghum raha hai :D
2014-09-24 Message generation fix
2014-09-24 OpenCV partial skeleton
2014-10-11 test
2015-03-04 mobility vhdl project updated
2015-03-04 almost final skeleton
2015-03-04 almost final skeleton for mobility on cpld
2015-03-24 blah
